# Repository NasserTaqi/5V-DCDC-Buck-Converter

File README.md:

# 5V DC-DC Buck Converter
A simple PCB of a 5V DC-DC buck converter with:
- input voltage range of 7V - 40V
- load current range of 0.2A - 3A
- 80% efficiency

## Board Setup
The board is made up of two layers and has the following stack-up:

Layer 1: Signal + GND pour

Layer 2: GND

### Schematic:

### PCB Layout

### PCB 3D

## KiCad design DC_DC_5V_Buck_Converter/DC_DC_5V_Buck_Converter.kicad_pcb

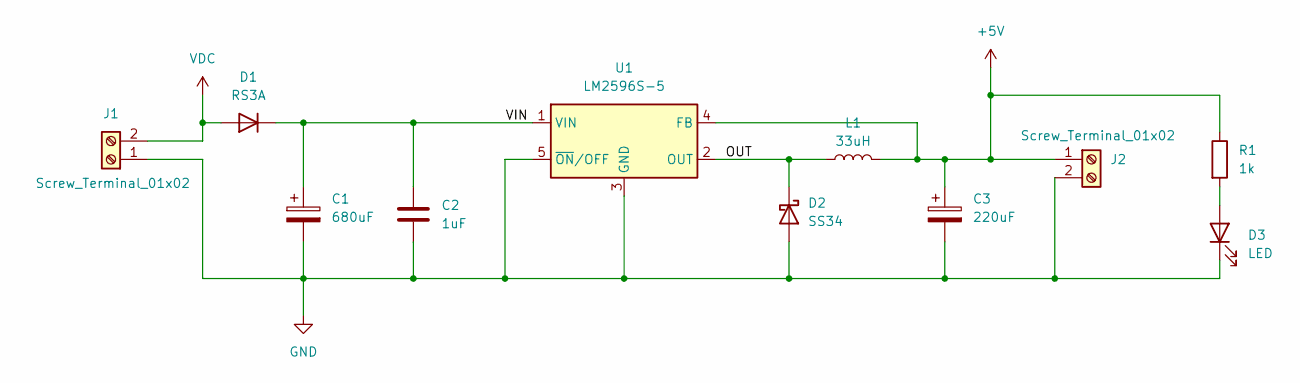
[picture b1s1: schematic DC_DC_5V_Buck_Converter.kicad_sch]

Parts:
C1: 680uF; CP_Elec_10x12.5; Manufacturer Part Number GYF1E681MCQ1GS
C2: 1uF; C_1206_3216Metric; Manufacturer Part Number CC1206ZRY5V7BB105
C3: 220uF; CP_Elec_10x12.5; Manufacturer Part Number GYF1H221MCQ1GS
D1: RS3A; D_SMC; Manufacturer Part Number RS3A
D2: SS34; D_SMC; Manufacturer Part Number SS34
D3: LED; LED_0805_2012Metric; Manufacturer Part Number Q62702P5178
J1, J2: Screw_Terminal_01x02; TerminalBlock_bornier-2_P5.08mm; Manufacturer Part Number 5452261
L1: 33uH; L_12x12mm_H8mm; Manufacturer Part Number 744770133
R1: 1k; R_0805_2012Metric; Manufacturer Part Number AT0805BRD071KL
U1: LM2596S-5; TO-263-5_TabPin3; Manufacturer Part Number LM2596S-5.0/NOPB

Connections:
+5V: C3.1, J2.1, L1.2, R1.1, U1.4 (FB)
/OUT: D2.1 (K), L1.1, U1.2 (OUT)
/VIN: C1.1, C2.1, D1.1 (K), U1.1 (VIN)
GND: C1.2, C2.2, C3.2, D2.2 (A), D3.1 (K), J1.1, J2.2, U1.3 (GND), U1.5 (~ON/OFF)
unnamed: D3.2 (A), R1.2
VDC: D1.2 (A), J1.2

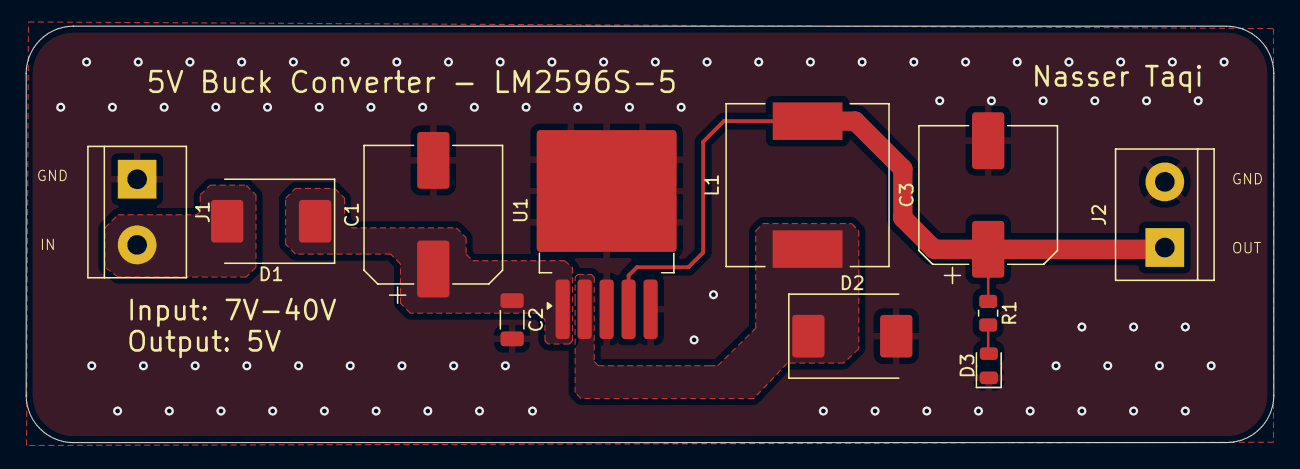
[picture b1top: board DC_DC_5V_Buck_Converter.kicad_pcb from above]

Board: 2 copper layers, 96.5 x 32.2 mm, 11 parts (0 on the bottom side), 6 nets.

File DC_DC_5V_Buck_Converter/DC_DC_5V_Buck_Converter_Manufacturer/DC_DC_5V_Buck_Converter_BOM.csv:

"Reference","Qty","Value","Footprint","Datasheet"
"C1","1","680uF","Capacitor_SMD:CP_Elec_10x12.5","~"
"C2","1","1uF","Capacitor_SMD:C_1206_3216Metric","~"
"C3","1","220uF","Capacitor_SMD:CP_Elec_10x12.5","~"
"D1","1","RS3A","Diode_SMD:D_SMC","https://mm.digikey.com/Volume0/opasdata/d220001/medias/docus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"
"D2","1","SS34","Diode_SMD:D_SMC","https://www.vishay.com/docs/88751/ss32.pdf"
"D3","1","LED","LED_SMD:LED_0805_2012Metric","~"
"J1,J2","2","Screw_Terminal_01x02","TerminalBlock:TerminalBlock_bornier-2_P5.08mm","~"
"L1","1","33uH","Inductor_SMD:L_12x12mm_H8mm","https://www.lcsc.com/datasheet/C143226.pdf"
"R1","1","1k","Resistor_SMD:R_0805_2012Metric","~"
"U1","1","LM2596S-5","Package_TO_SOT_SMD:TO-263-5_TabPin3","http://www.ti.com/lit/ds/symlink/lm2596.pdf"
